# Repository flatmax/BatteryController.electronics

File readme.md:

# Home networked battery controller electronics

V2.x Uses AC switching, I have started using Lithium ion electric bicycle batteries :
https://hackaday.io/project/182846-networked-home-battery-v2

V1.x was DC switching, that project used AGM batteries, find that project on "hack a day".

Provides a relay controller for a home networked battery system. The PCB has a Pi formatted 40 pin header.
There are 3 relays for controlling the AC positive lines on battery chargers.
There are 3 relays for controlling the AC positive lines on solar micro inverters.
There is a master/slave switch. This allows you to choose which networked battery is master. There can be only one.

See the file V1.0.TopLevel.schematic.jpg for a top level system diagram of v1.x of this project.
To come : v2.0.TopLevel.schematic.jpg, for now consult the sch file in KiCad.

## Controller software

Use the [BatteryController free software](https://github.com/flatmax/BatteryController) to operate this hardware.

## buildroot bootable SDCard image

Build an sdCard to boot off [using this buildroot external repo](https://github.com/Audio-Injector/RaspberryPi.buildroot.external/tree/BatteryController) for the Raspberry Pi.

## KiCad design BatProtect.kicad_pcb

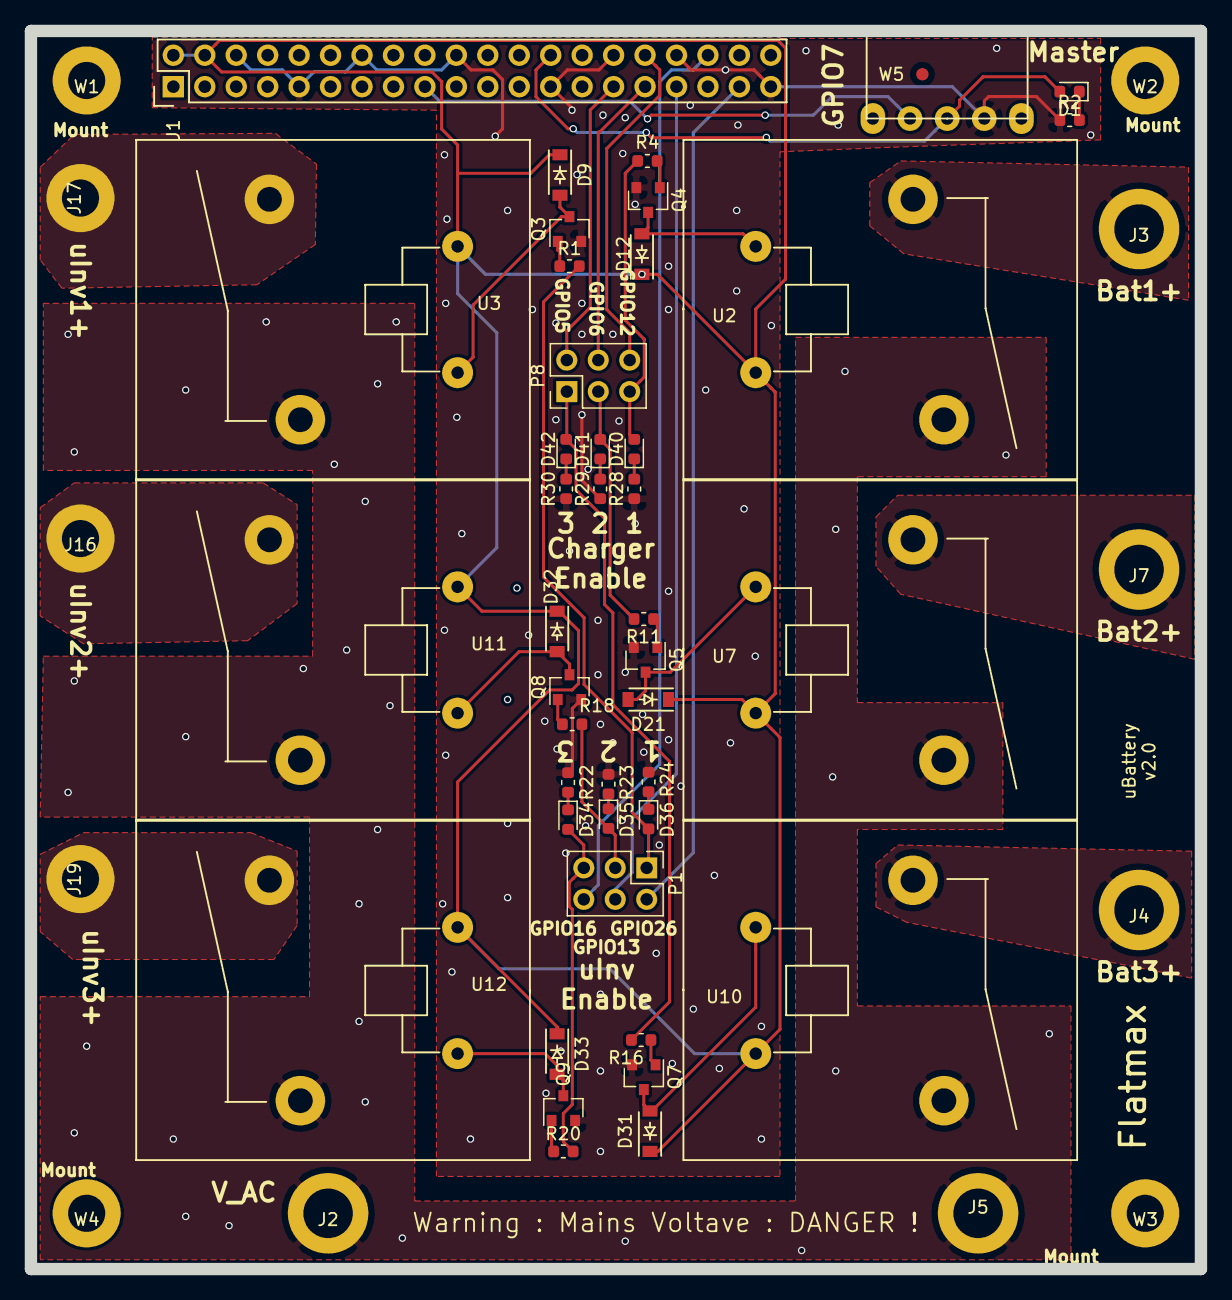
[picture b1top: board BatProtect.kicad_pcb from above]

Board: 2 copper layers, 94.5 x 100.0 mm, 55 parts (0 on the bottom side), 42 nets.

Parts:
D1, D34, D35, D36, D40, D41, D42: LED; LED_0603_1608Metric
D9, D12, D21, D31, D32, D33: 1N5819; SOD-123
J1: PC104; Pin_Header_Straight_2x20
J2, J5: VAC; Pin4mm
J3: BCharge1+; Pin4mm
J4: BCharge3+; Pin4mm
J7: BCharge2+; Pin4mm
J16: uInv2+; Pin3mm
J17: uInv1+; Pin3mm
J19: uInv3+; Pin3mm
P1, P8: CONN_02X03; PinHeader_2x03_P2.54mm_Vertical
Q3, Q4, Q5, Q7, Q8, Q9: MMBTA42; SOT-23
R1, R4, R11, R16, R18, R20: 220R; R_0603_1608Metric
R2, R22, R23, R24, R28, R29, R30: 3k3; R_0603_1608Metric
SW1: SW_SPDT; SS-12F23
U2, U3, U7, U10, U11, U12: SLA-05VDC-SL-A; SLA-4p
W1, W2, W3, W4: TEST_1P; Pin3mm
W5: Fiducial; Fiducial_1mm_Dia_2mm_Outer

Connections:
/29: J1.29, P8.2
/31: J1.31, P8.4
/32: J1.32, P8.6
/33: J1.33, P1.4
/36: J1.36, P1.6
/37: J1.37, P1.2
/Charge1Enable: D40.2, P8.5, R4.2
/Charge2Enable: D41.2, P8.3, R11.2
/Charge3Enable: D42.2, P8.1, R16.2
/MasterSlave: D1.2, J1.26, SW1.2
/VBat1+: J3.1, U2.1
/VBat2+: J7.1, U7.1
/VBat3+: J4.1, U10.1
/V_AC: J2.1, J5.1, U2.3, U3.1, U7.3, U10.3, U11.1, U12.1
/uInv1+: J17.1, U3.3
/uInv1En: D36.2, P1.1, R1.2
/uInv2+: J16.1, U11.3
/uInv2En: D35.2, P1.3, R18.2
/uInv3+: J19.1, U12.3
/uInv3En: D34.2, P1.5, R20.2
DGND: J1.6, J1.9, J1.14, J1.20, J1.25, J1.30, J1.34, J1.39, Q3.2, Q4.2, Q5.2, Q7.2, Q8.2, Q9.2, R2.1, R22.1, R23.1, R24.1, R28.1, R29.1, R30.1, SW1.1
DVDD2: J1.17, SW1.3
unnamed: D1.1, R2.2
unnamed: D9.2, Q3.3, U3.5
unnamed: D12.2, Q4.3, U2.5
unnamed: D21.2, Q5.3, U7.5
unnamed: D31.2, Q7.3, U10.5
unnamed: D32.2, Q8.3, U11.5
unnamed: D33.2, Q9.3, U12.5
unnamed: D34.1, R22.2
unnamed: D35.1, R23.2
unnamed: D36.1, R24.2
unnamed: D40.1, R28.2
unnamed: D41.1, R29.2
unnamed: D42.1, R30.2
unnamed: Q3.1, R1.1
unnamed: Q4.1, R4.1
unnamed: Q5.1, R11.1
unnamed: Q7.1, R16.1
unnamed: Q8.1, R18.1
unnamed: Q9.1, R20.1
V5: D9.1, D12.1, D21.1, D31.1, D32.1, D33.1, J1.2, J1.4, U2.2, U3.2, U7.2, U10.2, U11.2, U12.2

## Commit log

2019-12-18 v1.6
2019-12-19 added a link to the softwrae in the readme.md
2019-12-19 updated the readme.md
2020-03-22 Switched to the Flatmax free hardware license.
2020-03-22 Added a top level schematic - for a system level description.
2020-04-05 updated the readme with a link to imgur
2021-04-29 v2.0 Changed to AC mains relay switching.
2021-12-01 Switched relay names.
2021-12-01 updated the readme and file names.

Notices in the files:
BatProtect.kicad_pcb:
available under the conditions of this Licence. The Documentation may
rights granted under this Licence. The Licensee warrants that it does
